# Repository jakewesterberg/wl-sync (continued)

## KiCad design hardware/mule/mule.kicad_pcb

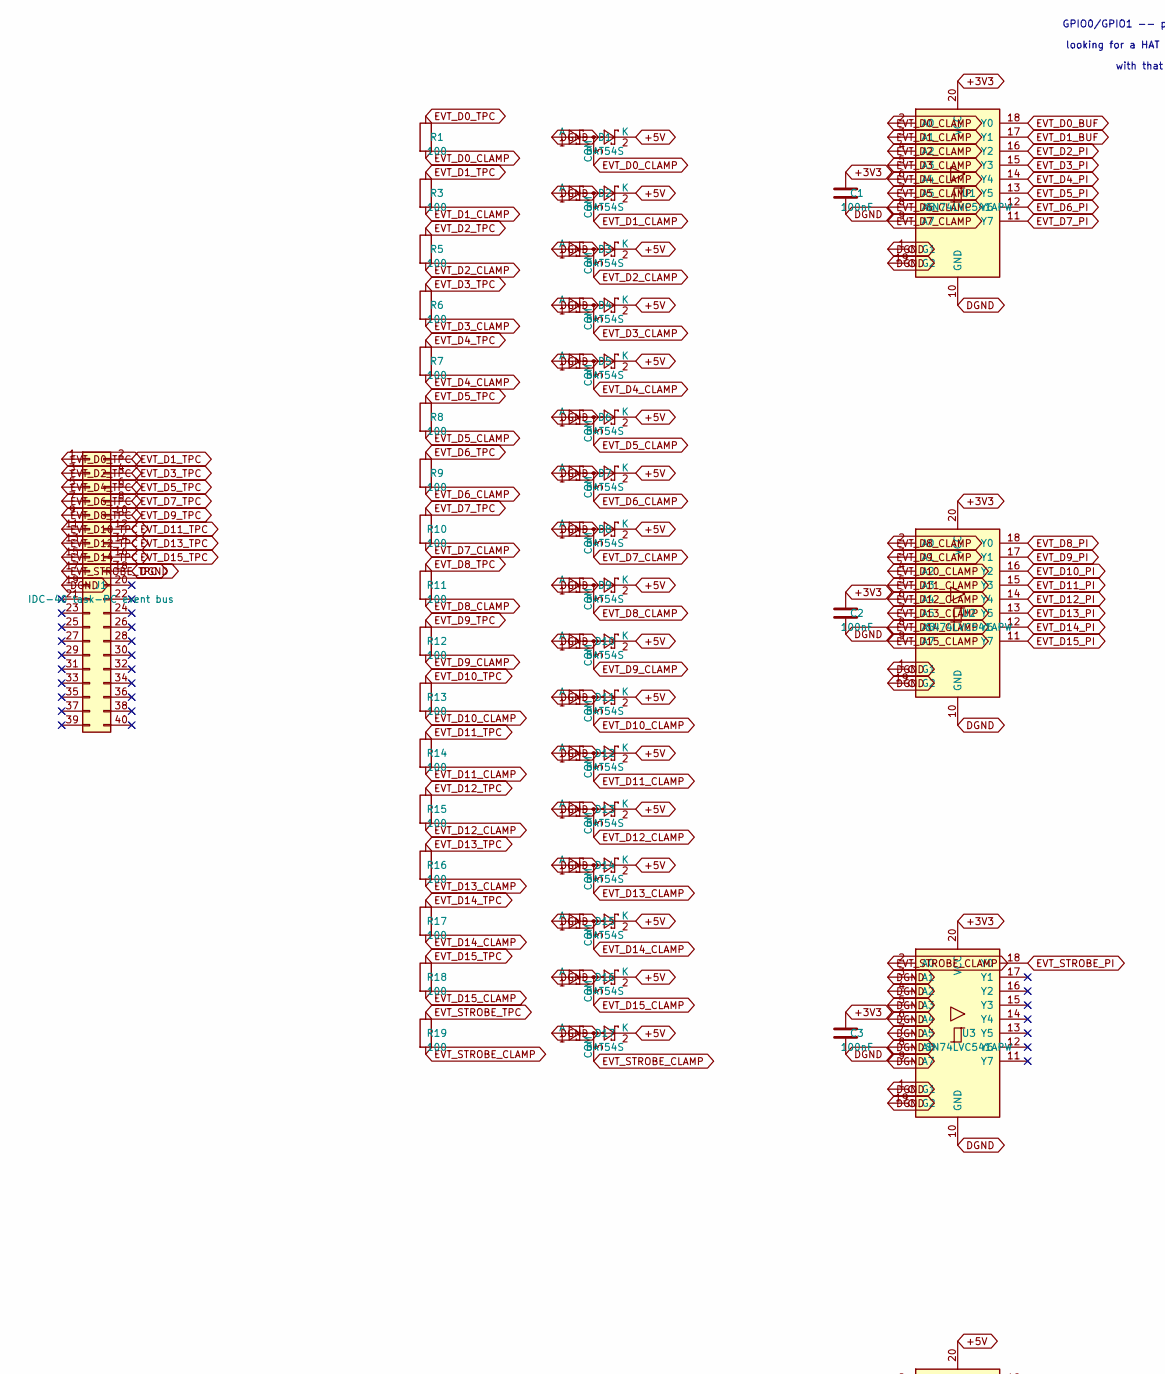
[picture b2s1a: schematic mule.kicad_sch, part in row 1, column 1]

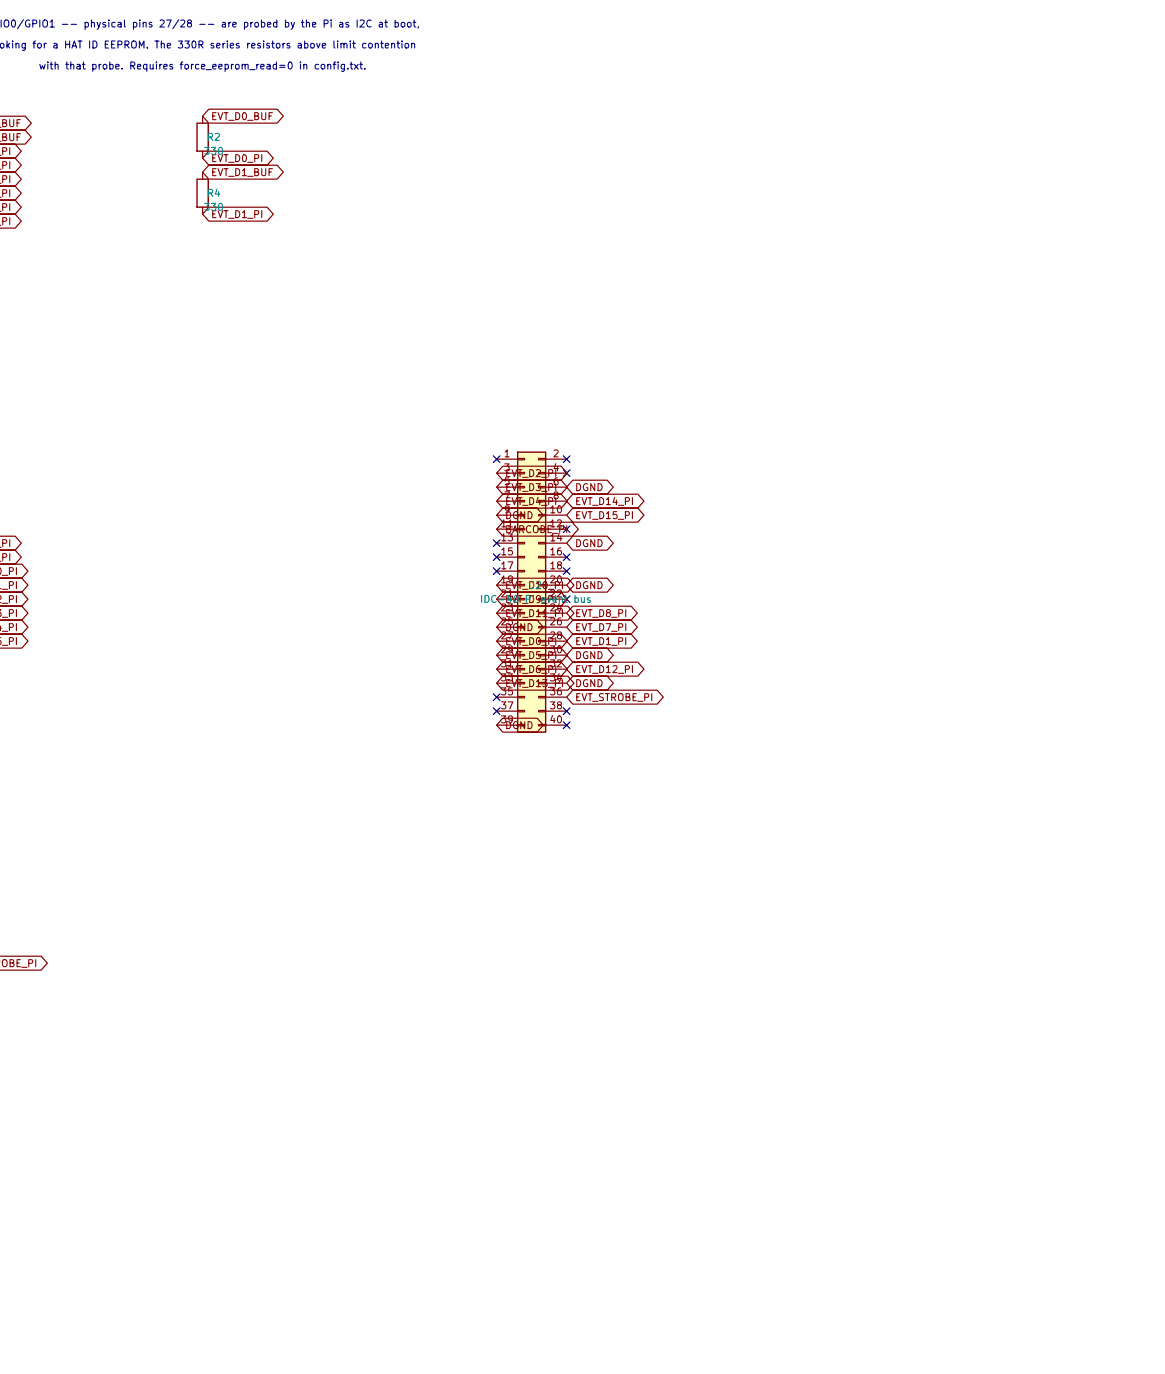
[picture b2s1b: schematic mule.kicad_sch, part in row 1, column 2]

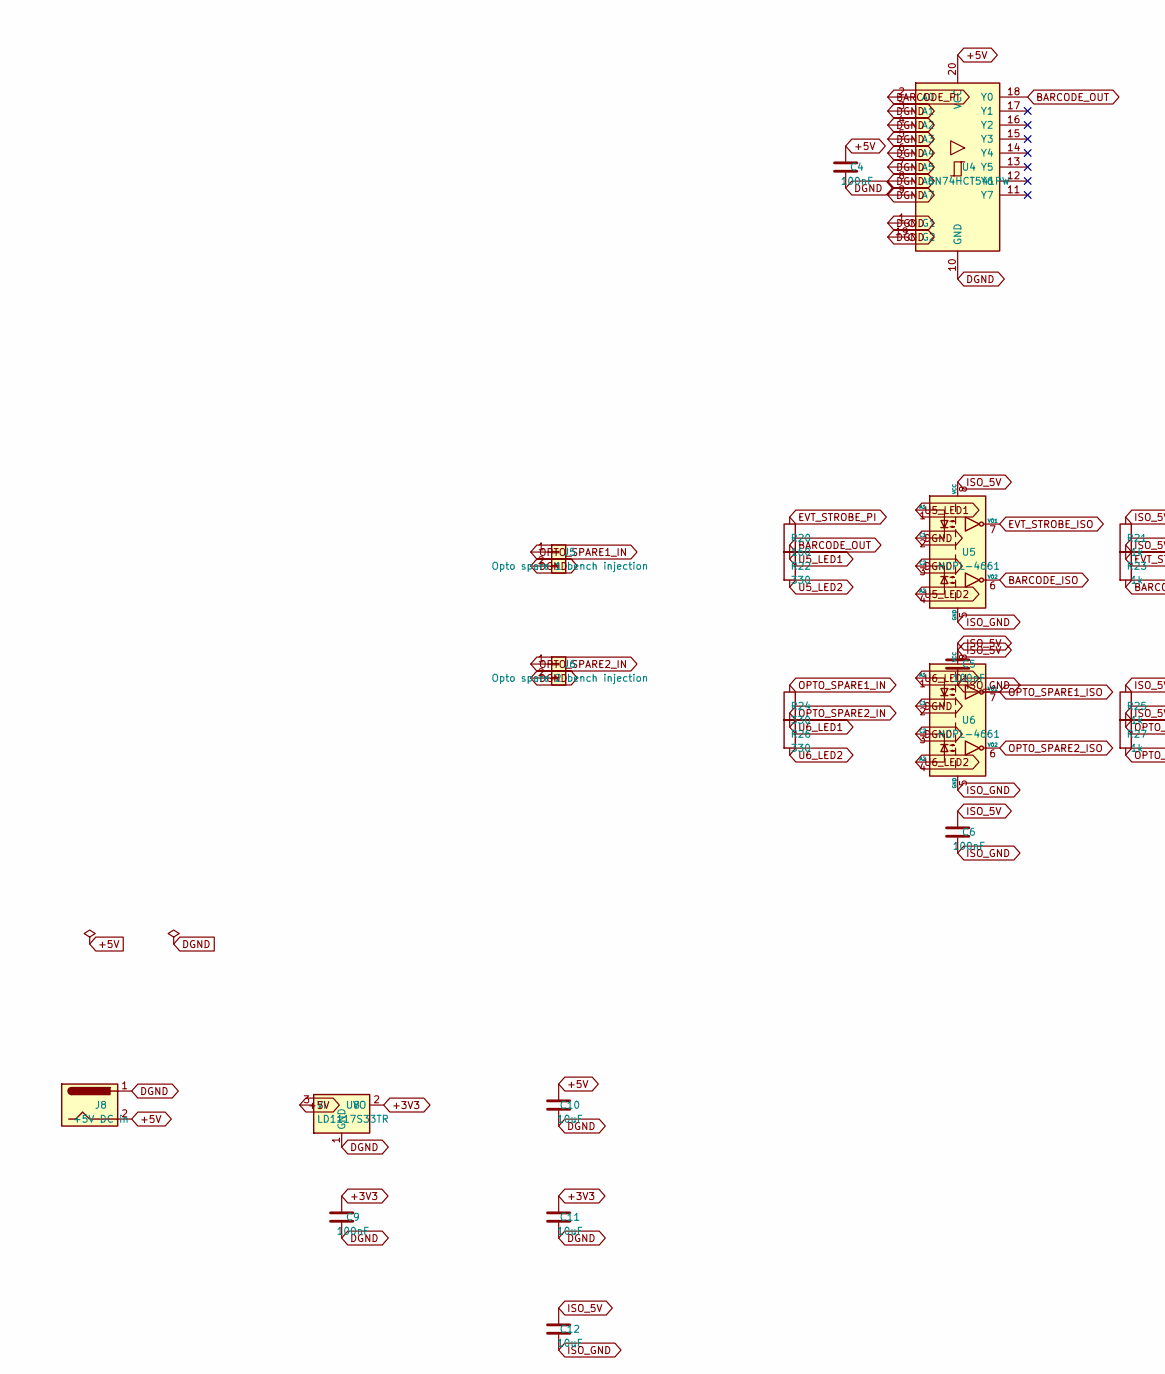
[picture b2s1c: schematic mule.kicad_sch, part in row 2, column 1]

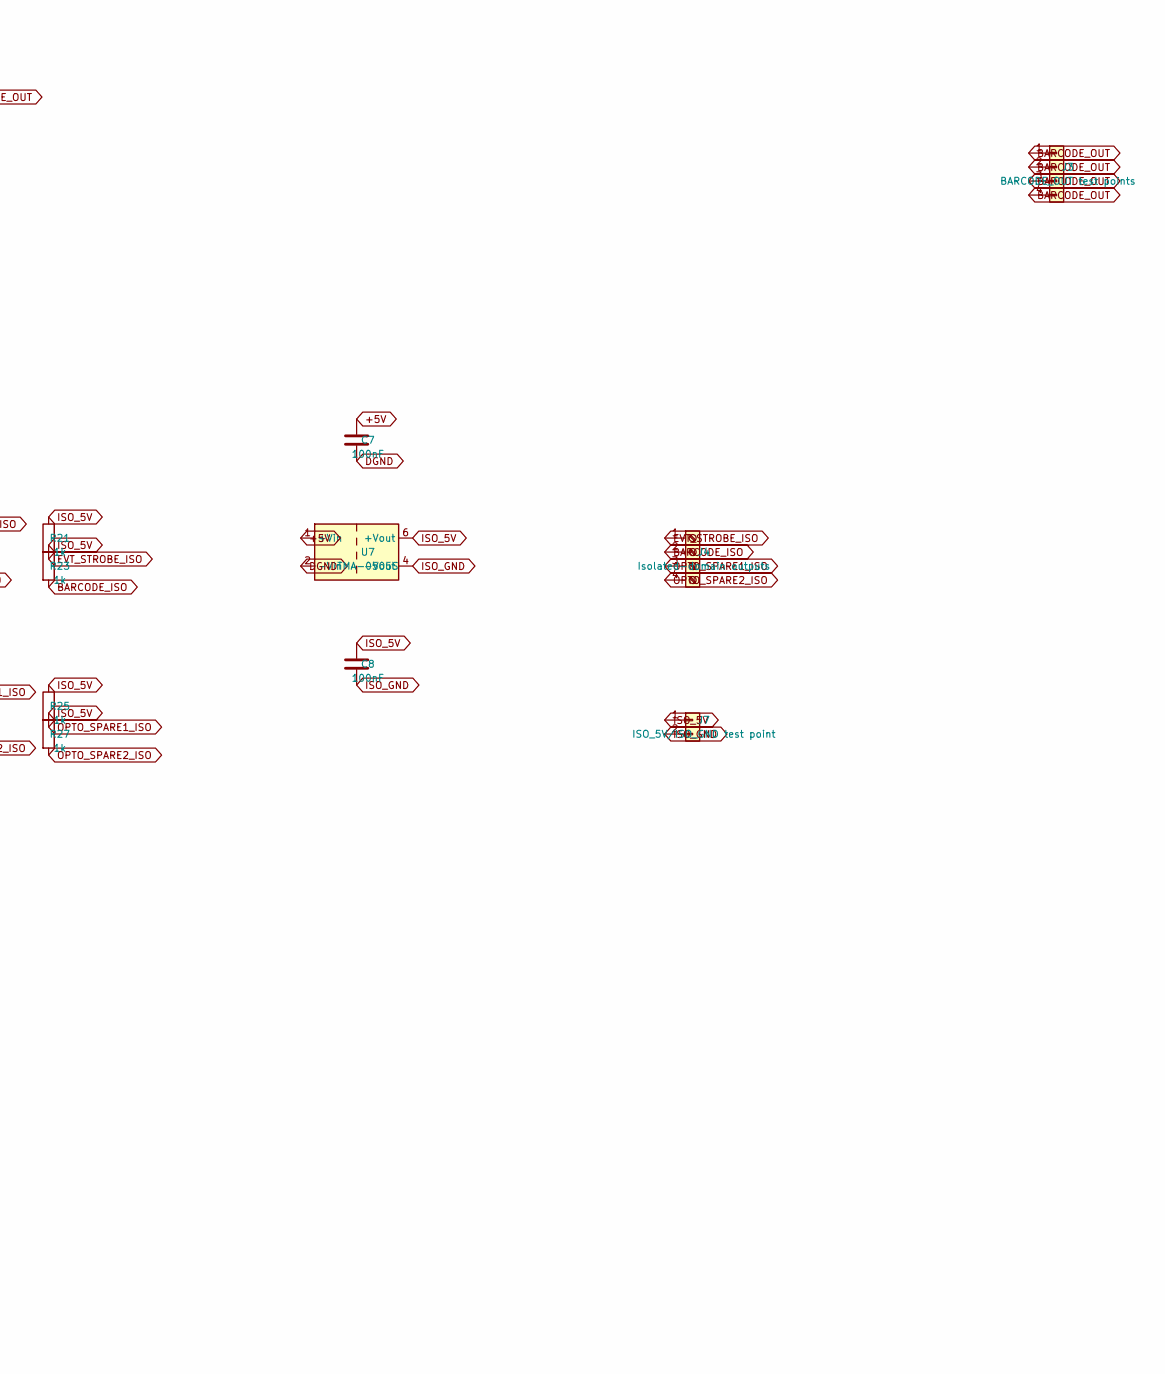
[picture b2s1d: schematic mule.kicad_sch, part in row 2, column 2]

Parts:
C1, C2, C3, C4, C5, C6, C7, C8, C9: 100nF; C_0603_1608Metric
C10, C11, C12: 10uF; C_0805_2012Metric
D1, D2, D3, D4, D5, D6, D7, D8, D9, D10, D11, D12, D13, D14, D15, D16, D17: BAT54S; SOT-23
J1: IDC-40 task-PC event bus; PinHeader_2x20_P2.54mm_Vertical
J2: IDC-40 Pi event bus; PinHeader_2x20_P2.54mm_Vertical
J3: BARCODE_OUT test points; PinHeader_1x04_P2.54mm_Vertical
J4: Isolated-domain outputs; TerminalBlock_Phoenix_MKDS-1,5-4_1x04_P5.00mm_Horizontal
J5: Opto spare 1 bench injection; PinHeader_1x02_P2.54mm_Vertical
J6: Opto spare 2 bench injection; PinHeader_1x02_P2.54mm_Vertical
J7: ISO_5V/ISO_GND test point; PinHeader_1x02_P2.54mm_Vertical
J8: +5V DC in; BarrelJack_CUI_PJ-102AH_Horizontal
R1, R3, R5, R6, R7, R8, R9, R10, R11, R12, R13, R14, R15, R16, R17, R18, R19: 100; R_0603_1608Metric
R2, R4, R22, R24, R26: 330; R_0603_1608Metric
R20: 160; R_0603_1608Metric
R21, R23, R25, R27: 1k; R_0603_1608Metric
U1, U2, U3: SN74LVC541APW; Texas_PW0020A_TSSOP-20_4.4x6.5mm_P0.65mm
U4: SN74HCT541PW; Texas_PW0020A_TSSOP-20_4.4x6.5mm_P0.65mm
U5, U6: HCPL-4661; DIP-8_W7.62mm
U7: TMA-0505S; Converter_DCDC_TRACO_TMA-05xxS_12xxS_Single_THT
U8: LD1117S33TR; SOT-223-3_TabPin2

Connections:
+3V3: C1.1, C2.1, C3.1, C9.1, C11.1, U1.20 (VCC), U2.20 (VCC), U3.20 (VCC), U8.2 (VO)
BARCODE_ISO: J4.2, R23.2, U5.6 (VO2)
BARCODE_OUT: J3.1, J3.2, J3.3, J3.4, R22.1, U4.18 (Y0)
BARCODE_PI: J2.11, U4.2 (A0)
EVT_D0_BUF: R2.1, U1.18 (Y0)
EVT_D0_CLAMP: D1.3 (COM), R1.2, U1.2 (A0)
EVT_D0_PI: J2.27, R2.2
EVT_D0_TPC: J1.1, R1.1
EVT_D1_BUF: R4.1, U1.17 (Y1)
EVT_D1_CLAMP: D2.3 (COM), R3.2, U1.3 (A1)
EVT_D1_PI: J2.28, R4.2
EVT_D1_TPC: J1.2, R3.1
EVT_D2_CLAMP: D3.3 (COM), R5.2, U1.4 (A2)
EVT_D2_PI: J2.3, U1.16 (Y2)
EVT_D2_TPC: J1.3, R5.1
EVT_D3_CLAMP: D4.3 (COM), R6.2, U1.5 (A3)
EVT_D3_PI: J2.5, U1.15 (Y3)
EVT_D3_TPC: J1.4, R6.1
EVT_D4_CLAMP: D5.3 (COM), R7.2, U1.6 (A4)
EVT_D4_PI: J2.7, U1.14 (Y4)
EVT_D4_TPC: J1.5, R7.1
EVT_D5_CLAMP: D6.3 (COM), R8.2, U1.7 (A5)
EVT_D5_PI: J2.29, U1.13 (Y5)
EVT_D5_TPC: J1.6, R8.1
EVT_D6_CLAMP: D7.3 (COM), R9.2, U1.8 (A6)
EVT_D6_PI: J2.31, U1.12 (Y6)
EVT_D6_TPC: J1.7, R9.1
EVT_D7_CLAMP: D8.3 (COM), R10.2, U1.9 (A7)
EVT_D7_PI: J2.26, U1.11 (Y7)
EVT_D7_TPC: J1.8, R10.1
EVT_D8_CLAMP: D9.3 (COM), R11.2, U2.2 (A0)
EVT_D8_PI: J2.24, U2.18 (Y0)
EVT_D8_TPC: J1.9, R11.1
EVT_D9_CLAMP: D10.3 (COM), R12.2, U2.3 (A1)
EVT_D9_PI: J2.21, U2.17 (Y1)
EVT_D9_TPC: J1.10, R12.1
EVT_D10_CLAMP: D11.3 (COM), R13.2, U2.4 (A2)
EVT_D10_PI: J2.19, U2.16 (Y2)
EVT_D10_TPC: J1.11, R13.1
EVT_D11_CLAMP: D12.3 (COM), R14.2, U2.5 (A3)
EVT_D11_PI: J2.23, U2.15 (Y3)
EVT_D11_TPC: J1.12, R14.1
EVT_D12_CLAMP: D13.3 (COM), R15.2, U2.6 (A4)
EVT_D12_PI: J2.32, U2.14 (Y4)
EVT_D12_TPC: J1.13, R15.1
EVT_D13_CLAMP: D14.3 (COM), R16.2, U2.7 (A5)
EVT_D13_PI: J2.33, U2.13 (Y5)
EVT_D13_TPC: J1.14, R16.1
EVT_D14_CLAMP: D15.3 (COM), R17.2, U2.8 (A6)
EVT_D14_PI: J2.8, U2.12 (Y6)
EVT_D14_TPC: J1.15, R17.1
EVT_D15_CLAMP: D16.3 (COM), R18.2, U2.9 (A7)
EVT_D15_PI: J2.10, U2.11 (Y7)
EVT_D15_TPC: J1.16, R18.1
EVT_STROBE_CLAMP: D17.3 (COM), R19.2, U3.2 (A0)
EVT_STROBE_ISO: J4.1, R21.2, U5.7 (VO1)
EVT_STROBE_PI: J2.36, R20.1, U3.18 (Y0)
EVT_STROBE_TPC: J1.17, R19.1
ISO_5V: C5.1, C6.1, C8.1, C12.1, J7.1, R21.1, R23.1, R25.1, R27.1, U5.8 (VCC), U6.8 (VCC), U7.6 (+Vout)
ISO_GND: C5.2, C6.2, C8.2, C12.2, J7.2, U5.5 (GND), U6.5 (GND), U7.4 (-Vout)
OPTO_SPARE1_IN: J5.1, R24.1
OPTO_SPARE1_ISO: J4.3, R25.2, U6.7 (VO1)
OPTO_SPARE2_IN: J6.1, R26.1
OPTO_SPARE2_ISO: J4.4, R27.2, U6.6 (VO2)
U5_LED1: R20.2, U5.1 (A1)
U5_LED2: R22.2, U5.4 (A2)
U6_LED1: R24.2, U6.1 (A1)
U6_LED2: R26.2, U6.4 (A2)

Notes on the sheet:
looking for a HAT ID EEPROM. The 330R series resistors above limit contention
with that probe. Requires force_eeprom_read=0 in config.txt.
GPIO0/GPIO1 -- physical pins 27/28 -- are probed by the Pi as I2C at boot,

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
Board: 2 copper layers, 72 parts (0 on the bottom side), 70 nets, no tracks yet.

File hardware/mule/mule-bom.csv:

"Reference","Value","Footprint","MPN","Qty"
"C1","100nF","Capacitor_SMD:C_0603_1608Metric","",""
"C2","100nF","Capacitor_SMD:C_0603_1608Metric","",""
"C3","100nF","Capacitor_SMD:C_0603_1608Metric","",""
"C4","100nF","Capacitor_SMD:C_0603_1608Metric","",""
"C5","100nF","Capacitor_SMD:C_0603_1608Metric","",""
"C6","100nF","Capacitor_SMD:C_0603_1608Metric","",""
"C7","100nF","Capacitor_SMD:C_0603_1608Metric","",""
"C8","100nF","Capacitor_SMD:C_0603_1608Metric","",""
"C9","100nF","Capacitor_SMD:C_0603_1608Metric","",""
"C10","10uF","Capacitor_SMD:C_0805_2012Metric","",""
"C11","10uF","Capacitor_SMD:C_0805_2012Metric","",""
"C12","10uF","Capacitor_SMD:C_0805_2012Metric","",""
"D1","BAT54S","Package_TO_SOT_SMD:SOT-23","",""
"D2","BAT54S","Package_TO_SOT_SMD:SOT-23","",""
"D3","BAT54S","Package_TO_SOT_SMD:SOT-23","",""
"D4","BAT54S","Package_TO_SOT_SMD:SOT-23","",""
"D5","BAT54S","Package_TO_SOT_SMD:SOT-23","",""
"D6","BAT54S","Package_TO_SOT_SMD:SOT-23","",""
"D7","BAT54S","Package_TO_SOT_SMD:SOT-23","",""
"D8","BAT54S","Package_TO_SOT_SMD:SOT-23","",""
"D9","BAT54S","Package_TO_SOT_SMD:SOT-23","",""
"D10","BAT54S","Package_TO_SOT_SMD:SOT-23","",""
"D11","BAT54S","Package_TO_SOT_SMD:SOT-23","",""
"D12","BAT54S","Package_TO_SOT_SMD:SOT-23","",""
"D13","BAT54S","Package_TO_SOT_SMD:SOT-23","",""
"D14","BAT54S","Package_TO_SOT_SMD:SOT-23","",""
"D15","BAT54S","Package_TO_SOT_SMD:SOT-23","",""
"D16","BAT54S","Package_TO_SOT_SMD:SOT-23","",""
"D17","BAT54S","Package_TO_SOT_SMD:SOT-23","",""
"J1","IDC-40 task-PC event bus","Connector_PinHeader_2.54mm:PinHeader_2x20_P2.54mm_Vertical","",""
"J2","IDC-40 Pi event bus","Connector_PinHeader_2.54mm:PinHeader_2x20_P2.54mm_Vertical","",""
"J3","BARCODE_OUT test points","Connector_PinHeader_2.54mm:PinHeader_1x04_P2.54mm_Vertical","",""
"J4","Isolated-domain outputs","TerminalBlock_Phoenix:TerminalBlock_Phoenix_MKDS-1,5-4_1x04_P5.00mm_Horizontal","",""
"J5","Opto spare 1 bench injection","Connector_PinHeader_2.54mm:PinHeader_1x02_P2.54mm_Vertical","",""
"J6","Opto spare 2 bench injection","Connector_PinHeader_2.54mm:PinHeader_1x02_P2.54mm_Vertical","",""
"J7","ISO_5V/ISO_GND test point","Connector_PinHeader_2.54mm:PinHeader_1x02_P2.54mm_Vertical","",""
"J8","+5V DC in","Connector_BarrelJack:BarrelJack_CUI_PJ-102AH_Horizontal","",""
"R1","100","Resistor_SMD:R_0603_1608Metric","",""
"R2","330","Resistor_SMD:R_0603_1608Metric","",""
"R3","100","Resistor_SMD:R_0603_1608Metric","",""
"R4","330","Resistor_SMD:R_0603_1608Metric","",""
"R5","100","Resistor_SMD:R_0603_1608Metric","",""
"R6","100","Resistor_SMD:R_0603_1608Metric","",""
"R7","100","Resistor_SMD:R_0603_1608Metric","",""
"R8","100","Resistor_SMD:R_0603_1608Metric","",""
"R9","100","Resistor_SMD:R_0603_1608Metric","",""
"R10","100","Resistor_SMD:R_0603_1608Metric","",""
"R11","100","Resistor_SMD:R_0603_1608Metric","",""
"R12","100","Resistor_SMD:R_0603_1608Metric","",""
"R13","100","Resistor_SMD:R_0603_1608Metric","",""
"R14","100","Resistor_SMD:R_0603_1608Metric","",""
"R15","100","Resistor_SMD:R_0603_1608Metric","",""
"R16","100","Resistor_SMD:R_0603_1608Metric","",""
"R17","100","Resistor_SMD:R_0603_1608Metric","",""
"R18","100","Resistor_SMD:R_0603_1608Metric","",""
"R19","100","Resistor_SMD:R_0603_1608Metric","",""
"R20","160","Resistor_SMD:R_0603_1608Metric","",""
"R21","1k","Resistor_SMD:R_0603_1608Metric","",""
"R22","330","Resistor_SMD:R_0603_1608Metric","",""
"R23","1k","Resistor_SMD:R_0603_1608Metric","",""
"R24","330","Resistor_SMD:R_0603_1608Metric","",""
"R25","1k","Resistor_SMD:R_0603_1608Metric","",""
"R26","330","Resistor_SMD:R_0603_1608Metric","",""
"R27","1k","Resistor_SMD:R_0603_1608Metric","",""
"U1","SN74LVC541APW","Package_SO:Texas_PW0020A_TSSOP-20_4.4x6.5mm_P0.65mm","",""
"U2","SN74LVC541APW","Package_SO:Texas_PW0020A_TSSOP-20_4.4x6.5mm_P0.65mm","",""
"U3","SN74LVC541APW","Package_SO:Texas_PW0020A_TSSOP-20_4.4x6.5mm_P0.65mm","",""
"U4","SN74HCT541PW","Package_SO:Texas_PW0020A_TSSOP-20_4.4x6.5mm_P0.65mm","",""
"U5","HCPL-4661","Package_DIP:DIP-8_W7.62mm","",""
"U6","HCPL-4661","Package_DIP:DIP-8_W7.62mm","",""
"U7","TMA-0505S","Converter_DCDC:Converter_DCDC_TRACO_TMA-05xxS_12xxS_Single_THT","",""
"U8","LD1117S33TR","Package_TO_SOT_SMD:SOT-223-3_TabPin2","",""

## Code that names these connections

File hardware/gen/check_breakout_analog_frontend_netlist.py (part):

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buffer -- one wrong net label, invisible to ERC (still a fully-connected, 0-error netlist) --
would defeat the entire point of this sheet while looking correct at a glance. `verify()`
below re-derives, independently of gen_breakout_analog_frontend.py's own choices, exactly
which pin of which part is allowed to touch AGND directly (INA105's REF pin, the shell-bond
resistor's far end, the MIC discrete diff-amp's R4) and which pin must NOT (every difference/
transimpedance amplifier's own reference input) -- same "a checker that trusted the generator
would only be checking the generator against itself" discipline every prior checker in this
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
# Real TI INA105 datasheet pinout (SOIC-8/DIP-8, standard unity-gain application circuit) --
# re-derived from the part's own datasheet-standard pin assignment, not imported from the
# generator's own placement code. REF is the ONLY pin of this part legitimately tied to AGND.
INA105 = {"ref_pin": "1", "minus": "2", "plus": "3", "vneg": "4", "sense": "5", "out": "6", "vpos": "7"}

# OPA2197xD (dual op-amp) unit/pin roles -- fixed by the STOCK KICAD SYMBOL's own pin NAMES
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def _find_bridging_resistor(nets: dict[str, list[Node]], net_a: str, net_b: str) -> str:
    """The single R-prefixed reference with one pin on net_a and the other on net_b --
    same "identify by walking two known nets" technique every checker in this project uses
    (e.g. check_breakout_pi_interface_netlist.py's own GPIO0/1 series-resistor check).
    """
    check(net_a in nets, f"missing net: {net_a!r}")
    check(net_b in nets, f"missing net: {net_b!r}")
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            shield_net in nets,
            f"{name}: shield net {shield_net!r} does not exist as its own distinct net -- "
            f"if it collapsed onto bare AGND (KiCad's own netlist exporter merges same-net "
            f"labels under one chosen name, same as the +12V/AGND short this generator hit "
            f"and fixed during development), this is exactly what that merge looks like",
        )
        r_ref = _find_bridging_resistor(nets, shield_net, "AGND")
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        values.get(r_ref) == "10",
        f"ACCESIO_AGND: bond resistor {r_ref} should be '10' (ohms), found {values.get(r_ref)!r}",
    )
    accesio_agnd_pins = {n.pin for n in nets["ACCESIO_AGND"] if n.ref.startswith("J")}
    check(
        len(accesio_agnd_pins) == 19,
        f"ACCESIO_AGND: expected all 19 of the connector's own AGND pins present, found {len(accesio_agnd_pins)}",
    )
    return (
        f"All 10 BNC channels' own shield nodes reach AGND through a dedicated 10R "
        f"resistor (never directly); the ACCESIO connector's 19-pin AGND bundle is bonded "
        f"to AGND the same way."
    )

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# 10 ohm / DNP, populated at bring-up".
ACCESIO_CONNECTOR_VALUE_MARKER = "ACCES I/O USB-AO16-8A mating DB37"
ACCESIO_SHELL_NET = "ACCESIO_SHELL"
ACCESIO_SHELL_PIN = "SH"       # Connector_Dsub DSUB-37 "...Housed_MountingHolesOffset11.32mm":
                               # its two shell/mounting pads are both named "SH"
ACCESIO_SHELL_R_VALUE = "0R/10R"

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    check(len(conn) == 1, f"expected exactly 1 ACCESIO DB37 connector, found {conn}")
    j_ref = conn[0]
    shell_nets = sorted(name for name, nl in nets.items()
                        if any(n.ref == j_ref and n.pin == ACCESIO_SHELL_PIN for n in nl))
    check(
        shell_nets == [ACCESIO_SHELL_NET],
        f"{j_ref} shell (pin {ACCESIO_SHELL_PIN!r}) expected on its own net "
        f"{ACCESIO_SHELL_NET!r}, found {shell_nets or 'no net at all'} -- ruling R2: the "
        f"shell gets a net of its own and ONE selectable resistor position to AGND",
    )
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            f"the shell bond to bring-up; populated in the drawing, it is a bond in copper",
        )
    return (
        f"DB37 shell (ruling R2): {j_ref} pin {ACCESIO_SHELL_PIN!r} on its own net "
        f"{ACCESIO_SHELL_NET}, one resistor position {r_ref} ({ACCESIO_SHELL_R_VALUE!r}) "
        f"to AGND"
        + (", DNP." if dnp_refs is not None else " (DNP state not checked: no DNP data supplied).")
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
    (1) The 13 plain INA105 channels: pin 2 ("-") must be the channel's own reference node
        (its BNC shield, or ACCESIO_AGND for the six eye channels) and must NOT be AGND
        itself. Pin 1 (REF) IS allowed on AGND -- that is what lands the OUTPUT in the AGND
        domain, and is the one pin per instance this check does not flag.
    (2) The 2 photodiode TIAs: the non-inverting ("+") input must be the channel's own BNC
        shield, not AGND -- spec Sec.6.3.1 / module docstring topology 2's whole point.
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        minus_nodes = _nodes_on(nets, "AGND", ref)
        check(
            not any(n.pin == INA105["minus"] for n in minus_nodes),
            f"{name}: {ref}'s own '-' pin (reference input) is wired directly to AGND -- "
            f"it must reference its own shield/ACCESIO_AGND node instead (spec Sec.5.6); "
            f"this would defeat the whole point of receiving this channel differentially",
        )
        ref_nodes = _nodes_on(nets, "AGND", ref)
        check(
            any(n.pin == INA105["ref_pin"] for n in ref_nodes),
            f"{name}: {ref}'s own REF pin (1) is not on AGND -- its output would not land "
            f"in the AGND domain",
        )
        if name in ACCESIO_CHANNELS:
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        check(len(minus_refs) == 1, f"{name}: expected exactly 1 OPA2197xD summing-junction node on {clamp_net!r}, found {minus_refs}")
        ref = next(iter(minus_refs))
        check(
            not any(n.ref == ref and n.pin == unit["plus"] for n in nets.get("AGND", [])),
            f"{name}: {ref}'s own '+' pin (non-inverting reference) is wired directly to "
            f"AGND -- it must reference the shield node {shield_net!r} instead (spec "
            f"Sec.6.3.1 / module docstring topology 2), or shield-borne disturbance "
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
    check("A_MIC_DAP" in nets, "missing net: 'A_MIC_DAP' (mic discrete diff-amp's own non-inverting node)")
    check("A_MIC_DAP" != "AGND", "A_MIC_DAP node incorrectly identical to AGND")
    dap_opamp_pins = [n for n in nets["A_MIC_DAP"] if values.get(n.ref, "").startswith("OPA4197")]
    check(
        len(dap_opamp_pins) == 1 and dap_opamp_pins[0].pintype == "input",
        f"A_MIC_DAP: expected exactly 1 OPA4197xD 'input'-typed pin (the diff-amp's own "
        f"non-inverting input), found {dap_opamp_pins}",
    )
    # A resistor bridges the shield node to A_MIC_DAP (R3, spec Sec.5.6's shield-reference
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        "No front end's own differential-reference input ('-' on the 13 INA105 channels, "
        "'+' on the 2 photodiode TIAs, the mic's own discrete non-inverting node) is wired "
        "directly to AGND; each references its own shield/ACCESIO_AGND node instead, with "
        "only the one designed exception per channel (INA105's REF pin) actually touching AGND."
    )


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    da_pins = {n.pin for n in nets[da_out] if n.ref == quad_ref}
    s1_pins = {n.pin for n in nets[s1_out] if n.ref == quad_ref}
    final_pins = {n.pin for n in nets[final_out] if n.ref == quad_ref}
    check(len(da_pins) == 1, f"A_MIC_DA: expected exactly 1 {quad_ref} pin (the discrete diff-amp's own output), found {da_pins}")
    check(len(s1_pins) == 2, f"A_MIC_S1: expected exactly 2 {quad_ref} pins (Sallen-Key section 1's own out+minus follower), found {s1_pins}")
    check(len(final_pins) == 2, f"A_MIC: expected exactly 2 {quad_ref} pins (Sallen-Key section 2's own out+minus follower), found {final_pins}")
    check(
        da_pins.isdisjoint(s1_pins) and s1_pins.isdisjoint(final_pins) and da_pins.isdisjoint(final_pins),
        f"A_MIC: the discrete diff-amp and the two Sallen-Key sections must use three "
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    results = []

    # (1) THE central defect this checker exists to catch: an INA105 channel's own '-'
    # reference pin moved from its shield node directly onto AGND -- the exact
    # "differential receive silently simplified to a plain AGND-referenced buffer" failure
    # spec Sec.5.6 exists to prevent, still a fully-connected 0-error netlist.
    moved = copy.deepcopy(good_nets)
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    )
    victim = moved["A_AMB_SHLD"].pop(idx)
    moved["AGND"] = moved["AGND"] + [victim]
    msg = _assert_fails(moved, good_values, "wired directly to AGND", "A_AMB's INA105 '-' pin moved from its shield node onto bare AGND", dnp_refs=good_dnp)
    results.append(f"Plain-channel diff-amp '-' pin silently AGND-referenced instead of shield-referenced: caught -- {msg}")

    # (2) The photodiode-specific flavour of the same defect class: the TIA's own '+'
    # (non-inverting reference) moved from shield onto AGND.
    moved2 = copy.deepcopy(good_nets)
    unit = OPA2197_UNIT["A_PD1"]
    idx2 = next(i for i, n in enumerate(moved2["A_PD1_SHLD"]) if n.pin == unit["plus"])
    victim2 = moved2["A_PD1_SHLD"].pop(idx2)
    moved2["AGND"] = moved2["AGND"] + [victim2]
    msg = _assert_fails(moved2, good_values, "wired directly to AGND", "A_PD1's TIA '+' pin moved from shield onto bare AGND", dnp_refs=good_dnp)
    results.append(f"Photodiode TIA '+' pin silently AGND-referenced instead of shield-referenced: caught -- {msg}")
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
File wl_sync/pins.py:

"""The board's GPIO allocation, in one place.

Transcribed from spec Sec.4's own table. A bare pin number at a call site survives a
board change silently, which is this project's named recurring failure -- right about
the model, wrong about the board.
"""

from __future__ import annotations

CODE_DATA_BASE = 0
CODE_DATA_COUNT = 16
CODE_STROBE_PIN = 16
BARCODE_PIN = 17

# Camera frame-time inputs, one exposure strobe per camera group. These were spare
# until 2026-08-16; the cameras free-run, so this box records when they exposed rather
# than telling them when to. See hardware/breakout/frame-time-inputs.md.
FRAME_TIME_GPIO = {"cam_frame_eye": 26, "cam_frame_beh": 27}

GPIO_MAP: dict[str, int] = {
    **{f"evt_d{i}": CODE_DATA_BASE + i for i in range(CODE_DATA_COUNT)},
    "evt_strobe": CODE_STROBE_PIN,
    "barcode_out": BARCODE_PIN,
    # Spec Sec.4's table, rows 20-25. The netlist-checked primary source is
    # hardware/gen/gen_breakout_pi_interface.py's GPIO_PIN_SPEC, which carries these in
    # this order; the transposition risk here is silent (swapping pd1/pd2, rwd_cmd/
    # rwd_dlvr or stim_trig/acc_trig changes no pin COUNT and no test that checks
    # membership), so tests/test_pins.py asserts the whole dict rather than the keys.
    "pd1_comp": 20,
    "pd2_comp": 21,
    "rwd_cmd": 22,
    "rwd_dlvr": 23,
    "stim_trig": 24,
    "acc_trig": 25,
    **FRAME_TIME_GPIO,
}

# Individually-captured input transitions: everything above the contiguous capture
# window. GPIO18/19 are spare.
EDGE_PINS: tuple[int, ...] = (20, 21, 22, 23, 24, 25, 26, 27)

# What GPIO_MAP leaves free in GPIO0-27. The bench's stamp-machine controls claim one of
# these: claiming an allocated pin would take it from its owner (the check at
# wl_sync/rp1/backend.py:456-463).
SPARE_PINS: tuple[int, ...] = tuple(
    pin for pin in range(28) if pin not in GPIO_MAP.values()
)

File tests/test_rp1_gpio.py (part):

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    seen = []
    pump = EdgePump(on_edge=lambda g, l, t: seen.append(g), origin_ns=0)
    pump.handle([_FakeEvent(1, 20, True, 0)], read_at=1)
    pump.handle([_FakeEvent(9, 20, False, 1_000)], read_at=2)   # GPIO20's 2..8 lost
    pump.handle([_FakeEvent(10, 22, True, 2_000, line_seqno=1)], read_at=3)  # must arrive

    assert seen == [20, 20, 22], "capture stopped after a drop"
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

def _edge(seqno, stamp_us):
    """An edge on GPIO20, rising and falling in turn, as a line's edges do."""
    return _FakeEvent(seqno, 20, seqno % 2 == 1, stamp_us * 1_000)


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# lr->seqno), and that line's own IRQ thread later counts it on the line and puts it in
# the buffer (edge_irq_thread: line->line_seqno++, then linereq_put_event). Two lines'
# threads are not ordered, so the buffer can hold n+1 before n; one line's events reach
# it in that line's order. GPIO26 and GPIO27, the cameras' frame-time lines, fire
# together on every frame.


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    return _FakeEvent(seqno, gpio, rising, stamp_us * 1_000, line_seqno=line_seqno)


# Two cameras exposing together: the request's 1..7 alternate between GPIO26 and GPIO27,
# each line counting its own events and alternating rising and falling.
_FRAMES = {
    1: _ev(1, 26, 1, True), 2: _ev(2, 27, 1, True), 3: _ev(3, 26, 2, False),
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

def test_two_lines_out_of_order_within_one_read_are_not_a_drop():
    """GPIO27's IRQ thread put 5 in the buffer before GPIO26's put 4. Nothing was lost,
    and the tracker used to report three losses for it, one of them negative: "1 lost
    between 3 and 5", "-2 lost between 5 and 4", "1 lost between 4 and 6"."""
    from wl_sync.rp1.gpio import EdgePump
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    what could have done it."""
    from wl_sync.rp1 import gpio

    # GPIO27 counts on from 1 to 2 and its levels alternate: nothing on it says it lost
    # anything, so number 4 is a numbered interrupt that never arrived.
    events = [
        _ev(1, 26, 1, True), _ev(2, 27, 1, True), _ev(3, 26, 2, False),
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    pump = gpio.EdgePump(on_edge=lambda *_: None, origin_ns=0)
    _pump_through(pump, request, [50_000])
    error = pump.take_error()
    assert "2 edge event(s) lost (kernel buffer overflow on GPIO20" in str(error)
    assert isinstance(error, gpio.EdgeBufferOverflowError)
    assert error.overflowed == {20: 2} and error.lost == 2
    _pump_through(pump, request, [80_000])  # the window closes on numbers 3 and 4
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

def test_two_events_at_the_same_level_on_one_line_are_a_coalesced_loss():
    """GPIO20 fell twice in a row, and nothing in the numbers says so. RP1's chained
    handler writes IRQRESET once per pin per pass (rp1_gpio_irq_handler), which clears
    every edge latched on it, so a rise and a fall closer together than the hard IRQ's
    latency take one IRQ, one number, one event. The level is the witness: with both
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    assert isinstance(error, gpio.CoalescedEdgeError)
    assert error.coalesced == {20: 1, 26: 1} and error.lost == 2
    assert str(error).startswith(
        "2 edge event(s) lost (coalesced interrupts: 1 on GPIO20, 1 on GPIO26)"
    )
    _pump_through(pump, request, [80_000])
    assert pump.error is None
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

def test_a_merged_pair_is_one_coalesced_loss_on_its_line_not_two():
    """GPIO27 fell and rose again before its IRQ thread ran. Both hard IRQs took a
    number, 4 and 5; the thread ran once, so one event carries 5 and the level it found,
    high (edge_irq_thread reads the level, gpiod_get_value_cansleep). pinctrl-rp1 handles
    edge IRQs with handle_edge_irq, which leaves the line unmasked while the thread runs.
    Two rising events in a row on GPIO27 report the loss at once, on its line; number 4,
    between them, is that same loss and is not reported again when its window closes."""
    from wl_sync.rp1 import gpio

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    pump = gpio.EdgePump(on_edge=lambda *_: None, origin_ns=0)
    _pump_through(pump, request, [50_000])
    error = pump.take_error()
    assert "1 edge event(s) lost (coalesced interrupts on GPIO27)" in str(error)
    assert isinstance(error, gpio.CoalescedEdgeError)
    assert error.coalesced == {27: 1} and error.lost == 1
    _pump_through(pump, request, [80_000])
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

def test_the_irq_thread_race_that_reuses_a_number_loses_one_edges_level_not_a_count():
    """GPIO27's second hard IRQ landed while its thread was building the first event,
    after it had cleared the stamp and before it read the number (gpiolib-cdev.c L896,
    L913). The first event goes out with the second IRQ's number, 5, and the re-run
    sends the second edge with 5 again: number 4 is missing and 5 is doubled. Two edges,
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

def test_a_race_at_the_wrong_level_excuses_its_missing_number_once():
    """GPIO27's race at the wrong level: its first copy pairs with the event before it,
    and that pair already explains the missing number, 4. The repeat used to queue a
    second excuse for the same 4, and the spare one swallowed number 3, lost on GPIO21
    to a merge of three edges that leaves its levels alternating. Truth: one edge lost
    on GPIO27, one number nothing explains. Both are reported."""
    from wl_sync.rp1 import gpio

    first = [_ev(1, 21, 1, True), _ev(2, 27, 1, True)]
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

def test_a_race_on_a_lines_first_event_at_the_wrong_level_is_not_silent():
    """The race on GPIO20's very first event: there is no event before the first copy to
    pair with, so the repeat, whose level is the true one, is compared with it instead.
    Rising twice: the first copy carries the second edge's level, and the falling edge
    is lost from the record. The repeat explains the missing number."""
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

def test_a_level_read_ahead_of_its_own_irq_counts_two():
    """Pinned, as documented: GPIO20's second edge landed before the thread read the
    level for the first event, but its hard IRQ came after the thread took the first
    event's number. Two events, the right numbers and stamps, the first at the wrong
    level: two pairs at one level, so two are counted for one damaged edge."""
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

def test_a_reused_number_never_excuses_another_lines_edge_still_on_its_way():
    """The race on GPIO20 lost number 11. Between its two hard IRQs GPIO26 took 12 and
    GPIO27 took 13, and GPIO27's thread is slow: 13 arrives in the next read. The
    duplicate used to excuse the highest number missing below it, 13, the one still on
    its way; when 13 arrived there was nothing to fill, and 11 was reported lost though
    nothing was. An excuse now waits until the numbers in its range are final."""
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    top = _U32 - 1
    events = [
        _ev(top - 2, 26, top - 1, True), _ev(top - 1, 27, 7, True),
        _ev(0, 27, 8, False), _ev(top, 26, top, False),  # GPIO27's 0 before GPIO26's top
        _ev(1, 26, 0, True), _ev(2, 27, 9, True),
    ]
    request = _Request([events[:3], events[3:], None])
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

def test_known_limit_an_overflow_on_a_quiet_line_is_counted_twice():
    """WHAT IT CANNOT TELL, pinned. The buffer overflowed and threw away GPIO21's second
    event, number 3. GPIO21 does not fire again until long after the window has closed on
    3, so 3 is reported first as a loss on an unknown line; when GPIO21 next fires, its
    own numbers show the overflow, which is reported too. One edge, counted twice."""
    from wl_sync.rp1 import gpio

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

def test_known_limit_an_event_later_than_the_window_is_reported_lost_then_passed_on():
    """WHAT IT CANNOT TELL, pinned. GPIO26's thread buffered number 3 more than
    EDGE_STAMP_LAG_US after its stamp, past the window, which is the roll barrier's
    assumption failing. 3 is reported lost; when it does arrive it is passed on without
    a word. The stamp-lag witness counts it over its allowance, so the journal warns."""
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    """Cameras at 200 fps, and capture stops while the kernel still holds frame 6 and a
    real loss is held: number 11 never comes. With the cameras faster than EDGE_WAIT_S no
    wait times out, so a look that ended after a fixed number of passes forced its last
    read's gaps final. Its third pass read GPIO27's number 17 two microseconds before
    GPIO26's 16 arrived, and the end of a healthy frame was reported lost beside 11. The
    look now runs until the window has closed on every gap it holds: 16 arrives, and 11
    alone is reported."""
    from wl_sync.rp1 import gpio
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    for k in range(1, 16):
        frame = 1_000_000 + 5_000 * k
        n = 2 * k - 1 + (k >= 6)  # number 11 never comes
        early = k == 8  # GPIO27's thread first, by 2 us
        first, second = (42, 40) if early else (50, 50)
        arrivals.append((frame + first, _ev(n, 26, k, k % 2, frame)))
        arrivals.append((frame + second, _ev(n + 1, 27, k, k % 2, frame + 2)))
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

def test_a_race_and_a_merge_on_one_event_count_one_loss():
    """GPIO20 rose and fell (3, 4) before its thread ran, merged; a third edge's hard IRQ
    (5) landed while the thread built that event, after the stamp was cleared, and the
    thread had read the level before the third edge: the first copy is falling, A's
    level, and pairs with the falling event before it; the repeat is rising, B's. Two
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

def test_an_overflow_is_written_just_before_the_event_that_shows_it(tmp_path):
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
